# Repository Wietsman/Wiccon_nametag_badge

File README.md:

# Wiccon_nametag_badge

## License

This hardware design may be used under the terms of the CERN-OHL-P license.

The Badge.Team mascots logo is all rights reserved and may not be reproduced.

## Authors
 - Wietse Boonstra
 - Renze Nicolai

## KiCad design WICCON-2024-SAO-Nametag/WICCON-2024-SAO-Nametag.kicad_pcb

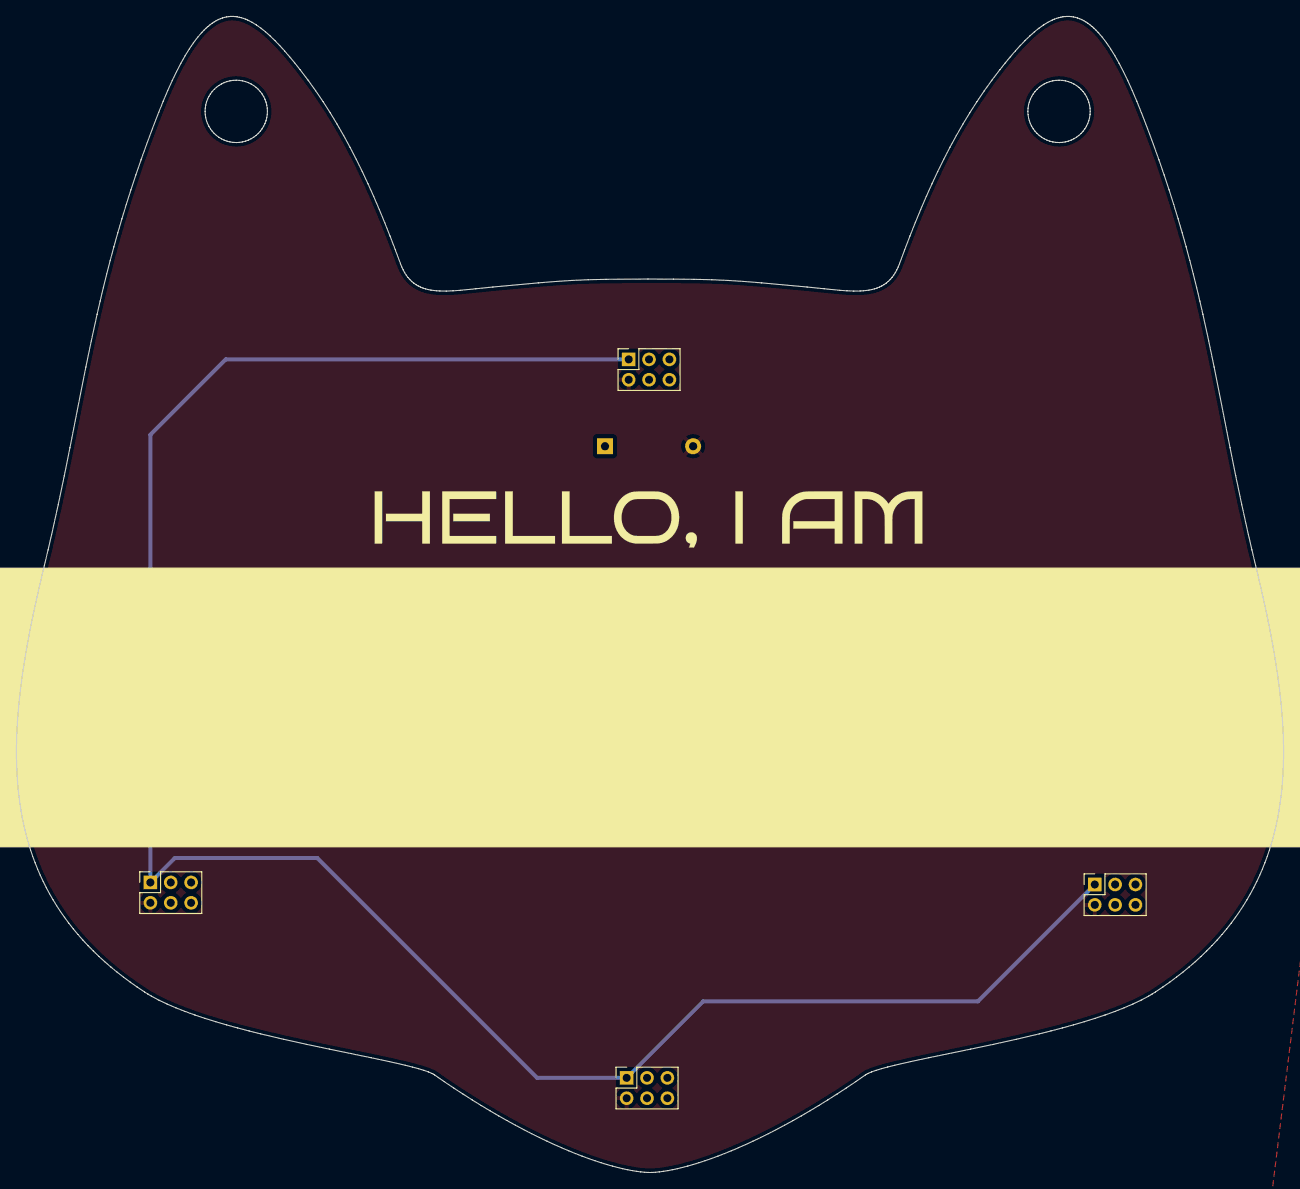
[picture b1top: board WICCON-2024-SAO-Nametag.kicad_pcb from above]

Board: 2 copper layers, 158.1 x 144.3 mm, 6 parts (1 on the bottom side), 2 nets.

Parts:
BT2: Battery; BatteryHolder_Keystone_2468_2xAAA
J1, J2, J3, J4: Conn_02x03_Odd_Even; PinSocket_2x03_P2.54mm_Vertical
N1: NameTag; badge-1(1)

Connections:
+3.3V: J1.1, J2.1, J3.1, J4.1
GND: BT2.2 (-), J1.2, J2.2, J3.2, J4.2

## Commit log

2024-08-30 first
